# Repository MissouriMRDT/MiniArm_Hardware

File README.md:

# Mini Arm
This project is for building a miniature arm that can sense its position, then send those positions to the rover for easier control on large motions.
The mini arm is primarily intended for use with PR events or during SAR.

[Main Project Document](https://mailmissouri.sharepoint.com/:w:/r/sites/SDELC-MarsRoverDesignTeam-Ogrp/_layouts/15/Doc.aspx?sourcedoc=%7BB2300151-E31F-458A-B07E-FE095C9D6675%7D&file=Mini%20Arm.docx&action=default&mobileredirect=true)

[Discord Forum](https://discord.com/channels/988649090306961418/1396668610507706429)

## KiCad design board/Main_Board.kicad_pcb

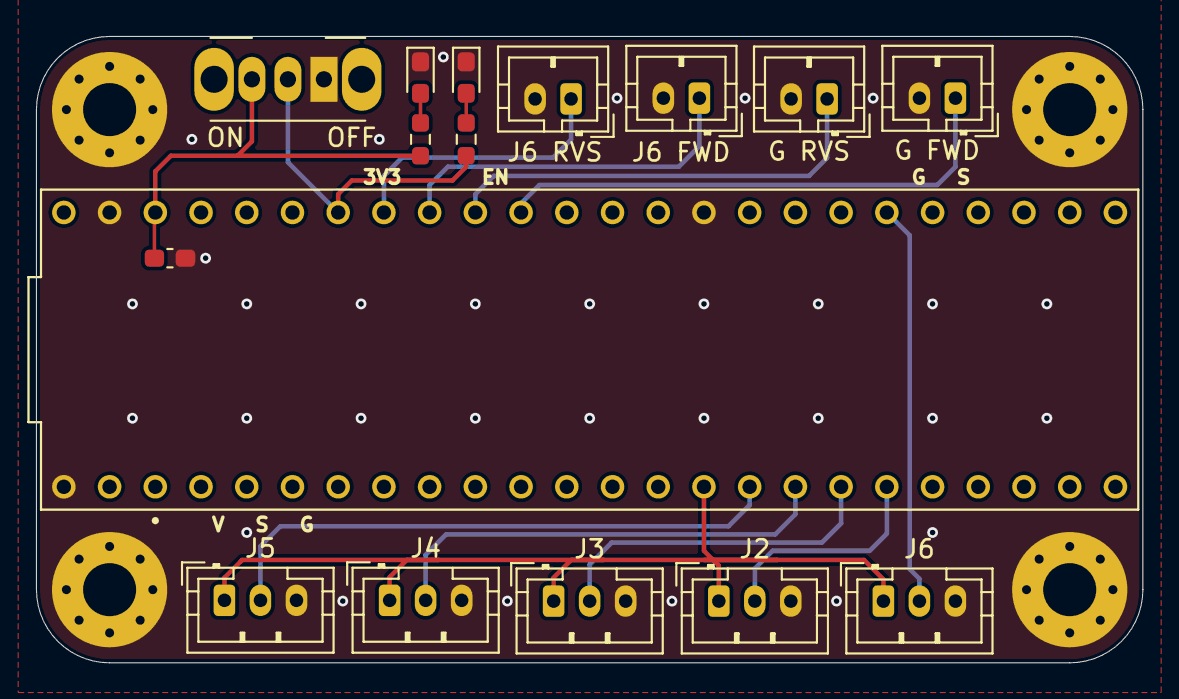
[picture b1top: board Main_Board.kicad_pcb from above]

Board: 2 copper layers, 61.5 x 34.8 mm, 20 parts (0 on the bottom side), 14 nets.

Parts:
C1: 4.7u; C_0603_1608Metric_Pad1.08x0.95mm_HandSolder
D1: GREEN; LED_0603_1608Metric_Pad1.05x0.95mm_HandSolder
D3: BLUE; LED_0603_1608Metric_Pad1.05x0.95mm_HandSolder
H1, H2, H3, H4: MountingHole; 4_40_Hole_Pad_Via
J1, J7, J8, J9: Conn_01x02_Pin; JST_PH_B2B-PH-K_1x02_P2.00mm_Vertical
J2: J2 Encoder; JST_PH_B3B-PH-K_1x03_P2.00mm_Vertical
J3: J3 Encoder; JST_PH_B3B-PH-K_1x03_P2.00mm_Vertical
J4: J4 Encoder; JST_PH_B3B-PH-K_1x03_P2.00mm_Vertical
J5: Pitch Encoder; JST_PH_B3B-PH-K_1x03_P2.00mm_Vertical
J6: X Encoder; JST_PH_B3B-PH-K_1x03_P2.00mm_Vertical
R1: 330; R_0603_1608Metric_Pad0.98x0.95mm_HandSolder
R2: 200; R_0603_1608Metric_Pad0.98x0.95mm_HandSolder
SW1: Enable Switch; SW_Slide_SPDT_Angled_CK_OS102011MA1Q
U1: Teensy4.1_DEV-16771; Teensy_4_1_Bare

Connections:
+3V3: C1.1, J2.1, J3.1, J4.1, J5.1, J6.1, R1.1, SW1.3 (C), U1.3.3V_1 (3.3V), U1.3.3V_2 (3.3V)
AE1: J2.2, U1.27 (A13)
AE2: J3.2, U1.26 (A12)
AE3: J4.2, U1.25 (A11)
AE4: J5.2, U1.24 (A10)
Enable: R2.1, SW1.2 (B), U1.20 (A6)
GND: C1.2, D1.1 (K), D3.1 (K), H1.1, H2.1, H3.1, H4.1, J1.2, J2.3, J3.3, J4.3, J5.3, J6.3, J7.2, J8.2, J9.2, SW1.1 (A), U1.GND1 (GND), U1.GND2 (GND), U1.GND3 (GND)
Gripper_FWD: J1.1, U1.16 (A2)
Gripper_RVS: J7.1, U1.17 (A3)
unnamed: D1.2 (A), R1.2
unnamed: D3.2 (A), R2.2
Pot: J6.2, U1.38 (A14)
Roll_FWD: J8.1, U1.18 (A4)
Roll_RVS: J9.1, U1.19 (A5)

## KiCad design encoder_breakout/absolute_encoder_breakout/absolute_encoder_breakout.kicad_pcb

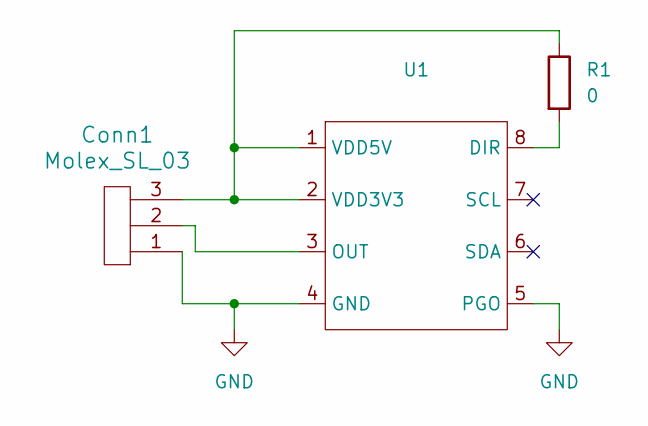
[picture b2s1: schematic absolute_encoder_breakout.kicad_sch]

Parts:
Conn1: Molex_SL_03; JST_PH_B3B-PH-K_1x03_P2.00mm_Vertical
R1: 0
U1: SOIC-8_3.9x4.9mm_P1.27mm

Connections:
GND: Conn1.1, U1.4 (GND), U1.5 (PGO)
unnamed: R1.2, U1.8 (DIR)
unnamed: Conn1.2, U1.3 (OUT)
unnamed: Conn1.3, R1.1, U1.1 (VDD5V), U1.2 (VDD3V3)

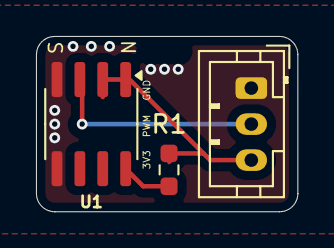
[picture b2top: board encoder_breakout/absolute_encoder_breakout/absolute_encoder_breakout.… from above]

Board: 2 copper layers, 14.5 x 9.7 mm, 3 parts (0 on the bottom side), 4 nets.

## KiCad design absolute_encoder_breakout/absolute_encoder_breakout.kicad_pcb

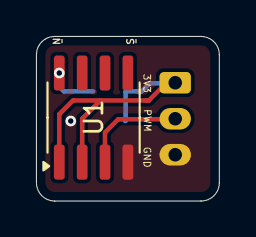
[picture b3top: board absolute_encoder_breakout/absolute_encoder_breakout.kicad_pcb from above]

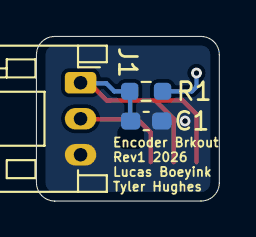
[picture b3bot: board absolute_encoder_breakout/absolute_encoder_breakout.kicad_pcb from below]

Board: 2 copper layers, 10.2 x 9.1 mm, 4 parts (3 on the bottom side), 4 nets.

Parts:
C1: 10uF; C_0603_1608Metric_Pad1.08x0.95mm_HandSolder
J1: Conn_01x03_Pin; JST_PH_S3B-PH-K_1x03_P2.00mm_Horizontal
R1: 0; R_0603_1608Metric_Pad0.98x0.95mm_HandSolder
U1: SOIC-8_3.9x4.9mm_P1.27mm

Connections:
GND: C1.2, J1.3, U1.4 (GND)
unnamed: C1.1, J1.1, R1.1, U1.1 (VDD5V), U1.2 (VDD3V3)
unnamed: J1.2, U1.3 (OUT)
unnamed: R1.2, U1.8 (DIR)

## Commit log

2025-09-23 Add Absolute Encoder Symbol
2025-09-23 Added Breakout Board for A-Encoder
2025-09-26 Autosave
    Probably not important
2025-10-03 Main Board Schematic
2025-10-03 Schematic Finished
2025-10-03 Fix Schematic after Review
2025-10-03 Add Encoder PCB
2025-10-03 Move Power Indicators
2025-10-07 Fix Breakout Board
2025-10-09 Update Mini Arm Board
2025-10-15 Fix Breakout Schematic and Layout
2025-10-15 Fix Breakout
2025-10-16 Update Main Board
2025-10-30 add I2C bus, reverted encoder breakout
2025-10-30 Add main board general layout
2025-10-31 Complete main board pre-review
2025-11-01 Adjust main board size
2025-11-04 Final Encoder Breakout
2025-11-06 Adjust LED positions - fix DRC error
2025-11-07 Add signatures & ground vias
2025-11-10 Clean up before order
2025-11-11 Added github actions
2025-11-11 Add github workflow and reorganize breakout location
2025-11-11 Fix overlapping job names
2025-11-11 Remove possibly unsupported quotes
2025-11-11 Update encoder path
2025-11-11 Change board-path input
2025-11-11 Remove unnecessary env variable set
2025-11-11 Change trace width of enable signal
2025-11-11 Remove stub on 3v3
2025-11-11 Fixed via heart being too close together
2025-11-11 Add via stitching
2025-11-11 Fix text size on encoder breakout
2025-11-15 Add step file
2026-03-14 Add gripper and roll buttons
2026-03-16 Make switch pads GND
2026-03-21 Add plated mounting holes
2026-03-23 Final design files as ordered
